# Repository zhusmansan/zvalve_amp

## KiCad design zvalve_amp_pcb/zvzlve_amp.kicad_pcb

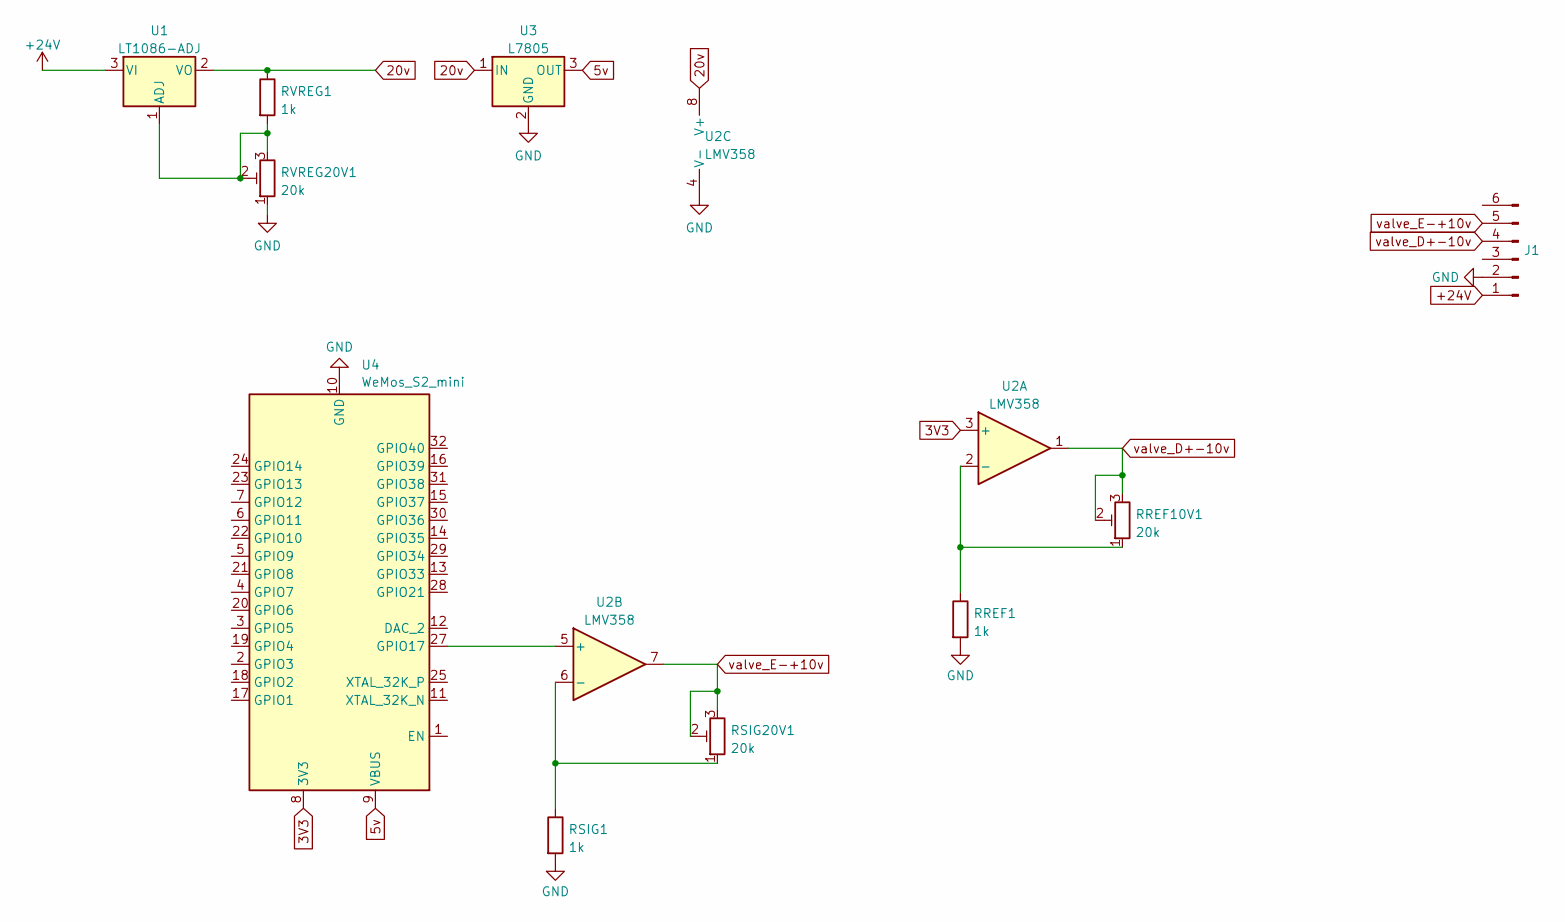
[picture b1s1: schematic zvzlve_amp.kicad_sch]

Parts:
J1: PinSocket_1x06_P2.54mm_Vertical
RREF1: 1k; R_0805_2012Metric
RREF10V1: 20k; Potentiometer_Bourns_3296W_Vertical
RSIG1: 1k; R_0805_2012Metric
RSIG20V1: 20k; Potentiometer_Bourns_3296W_Vertical
RVREG1: 1k; R_0805_2012Metric
RVREG20V1: 20k; Potentiometer_Bourns_3296W_Vertical
U1: LT1086-ADJ; TO-220-3_Vertical
U2: LMV358; DIP-8_W7.62mm
U3: L7805; TO-220-3_Vertical
U4: WeMos_S2_mini; WEMOS_S2_mini

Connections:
3V3: U2.3 (+), U4.8 (3V3)
5v: U3.3 (OUT), U4.9 (VBUS)
20v: RVREG1.1, U1.2 (VO), U2.8 (V+), U3.1 (IN)
+24V: J1.1, U1.3 (VI)
GND: J1.2, RREF1.2, RSIG1.2, RVREG20V1.1, U2.4 (V-), U3.2 (GND), U4.10 (GND), U4.26 (GND)
unnamed: RVREG1.2, RVREG20V1.2, RVREG20V1.3, U1.1 (ADJ)
unnamed: RREF1.1, RREF10V1.1, U2.2 (-)
unnamed: U2.5 (+), U4.27 (GPIO17)
unnamed: RSIG1.1, RSIG20V1.1, U2.6 (-)
valve_D+-10v: J1.4, RREF10V1.2, RREF10V1.3, U2.1
valve_E-+10v: J1.5, RSIG20V1.2, RSIG20V1.3, U2.7

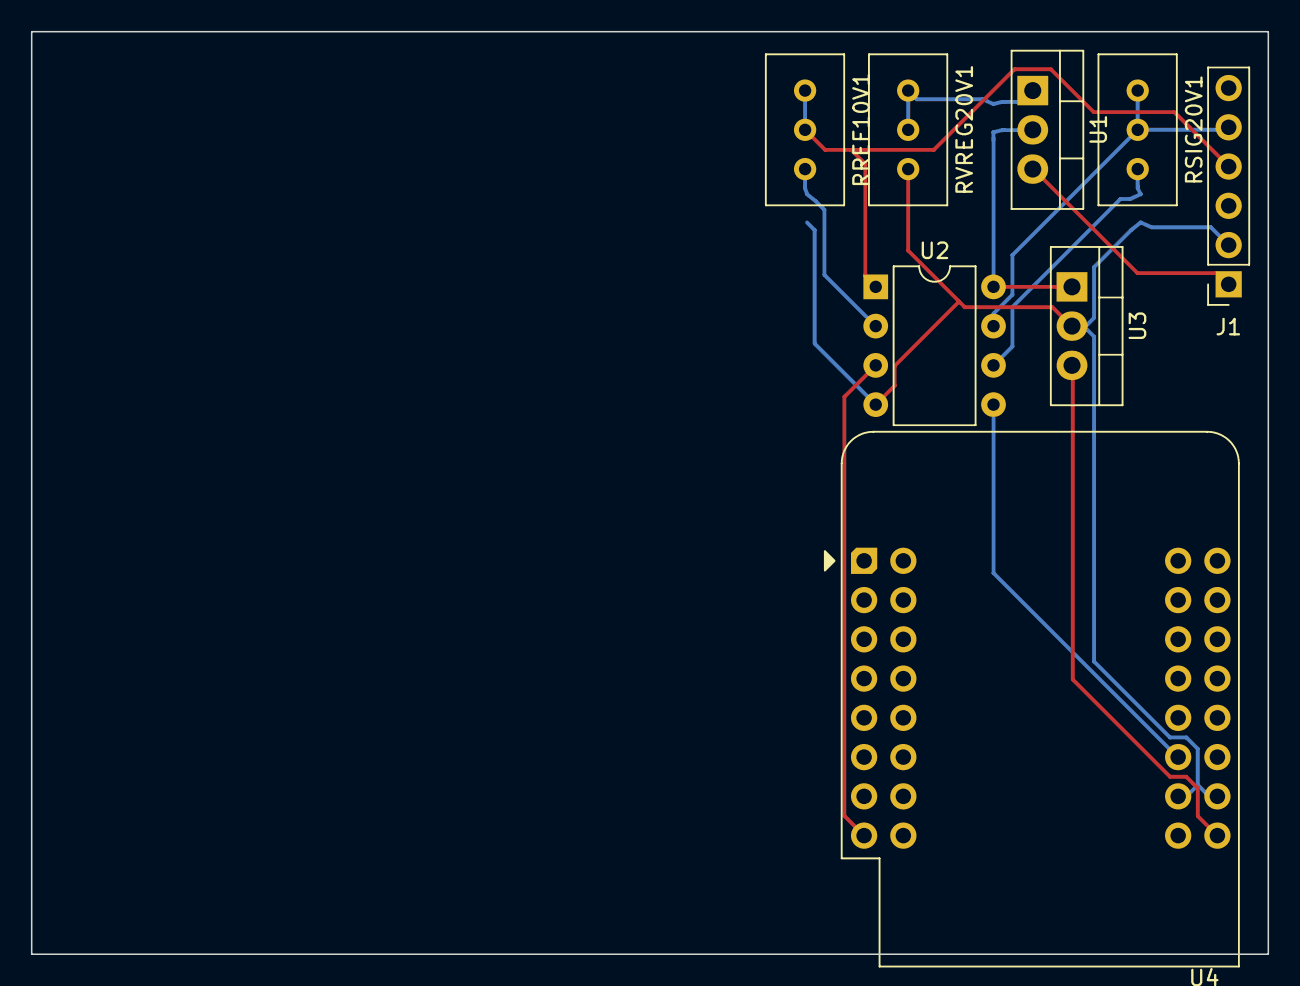
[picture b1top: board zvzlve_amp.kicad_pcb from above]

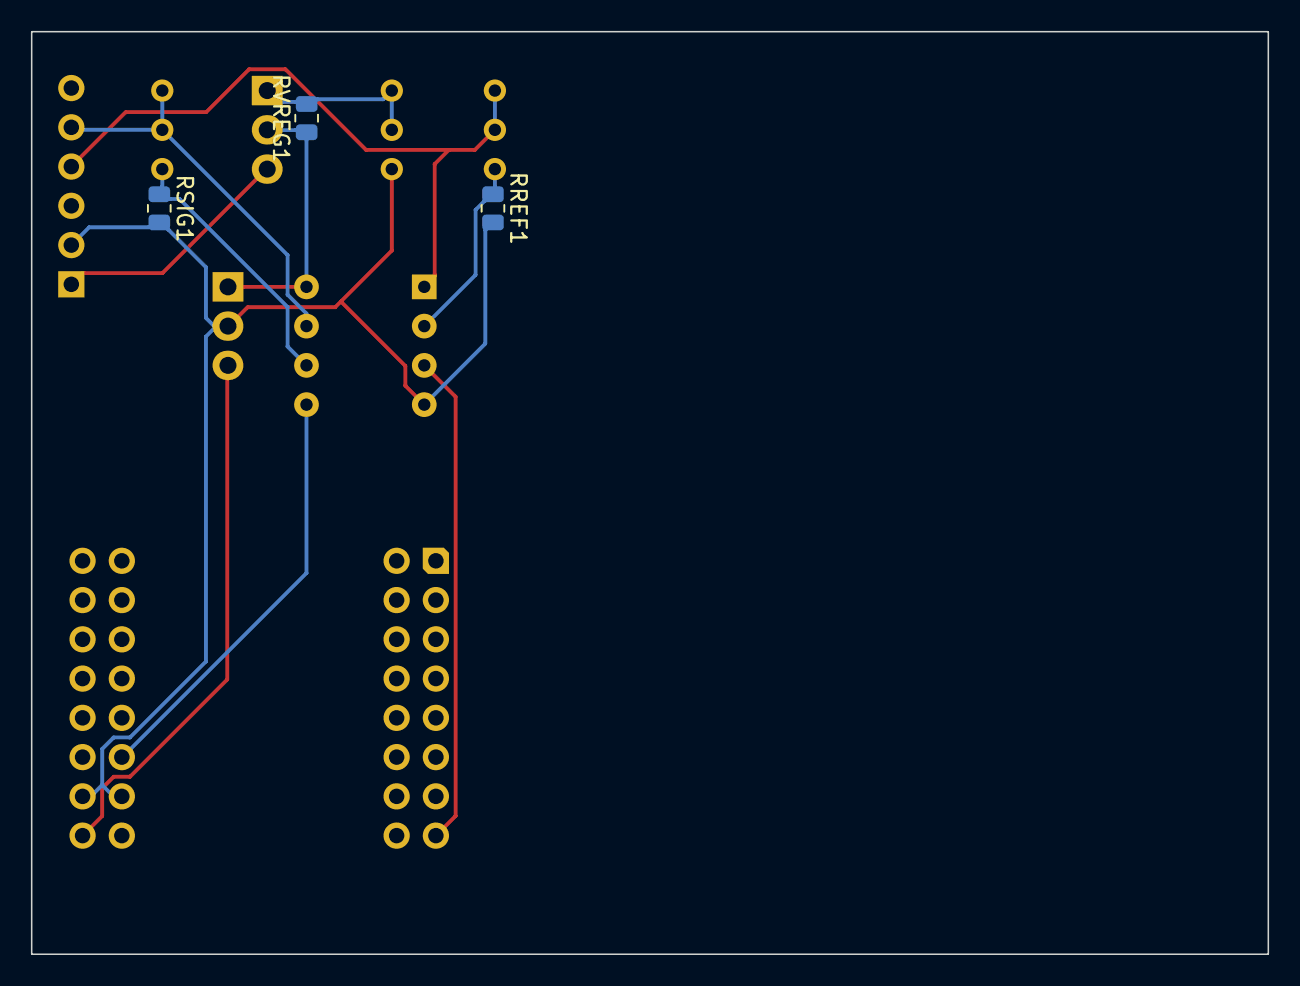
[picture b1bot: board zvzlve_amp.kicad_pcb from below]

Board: 2 copper layers, 80.0 x 59.7 mm, 11 parts (3 on the bottom side), 11 nets.

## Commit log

2024-07-14 Начальная версия
2024-07-14 Переименование
